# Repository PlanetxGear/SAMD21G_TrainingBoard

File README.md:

# Microchip SAMD21G Training Board for 「SAMファミリ活用ガイドブック」.
---
## Description
後閑哲也氏の著書[ＳＡＭファミリ活用ガイドブック][1](ISBN 978-4-297-11291-2)に出てくるトレーニングボードをKiCADで書き起こした回路図とガーバーデータです。
これは[KiCAD][2]によって描かれています。　この資料が皆さんの学習の一助となれば幸いです。

## Picture

## References.
 * <https://www.microchip.com/wwwproducts/en/ATsamd21g18>
 * <http://www.picfun.com/picbookZ3.html>
 * <https://gihyo.jp/book/2020/978-4-297-11291-2>

## Licence
[MIT]<https://en.wikipedia.org/wiki/MIT_License> <https://ja.wikipedia.org/wiki/MIT_License>

## Author
Hiroshi Murakami  
<https://www.planetxgear.com/>  

[1]: https://gihyo.jp/book/2020/978-4-297-11291-2 
[2]: https://kicad-pcb.org/

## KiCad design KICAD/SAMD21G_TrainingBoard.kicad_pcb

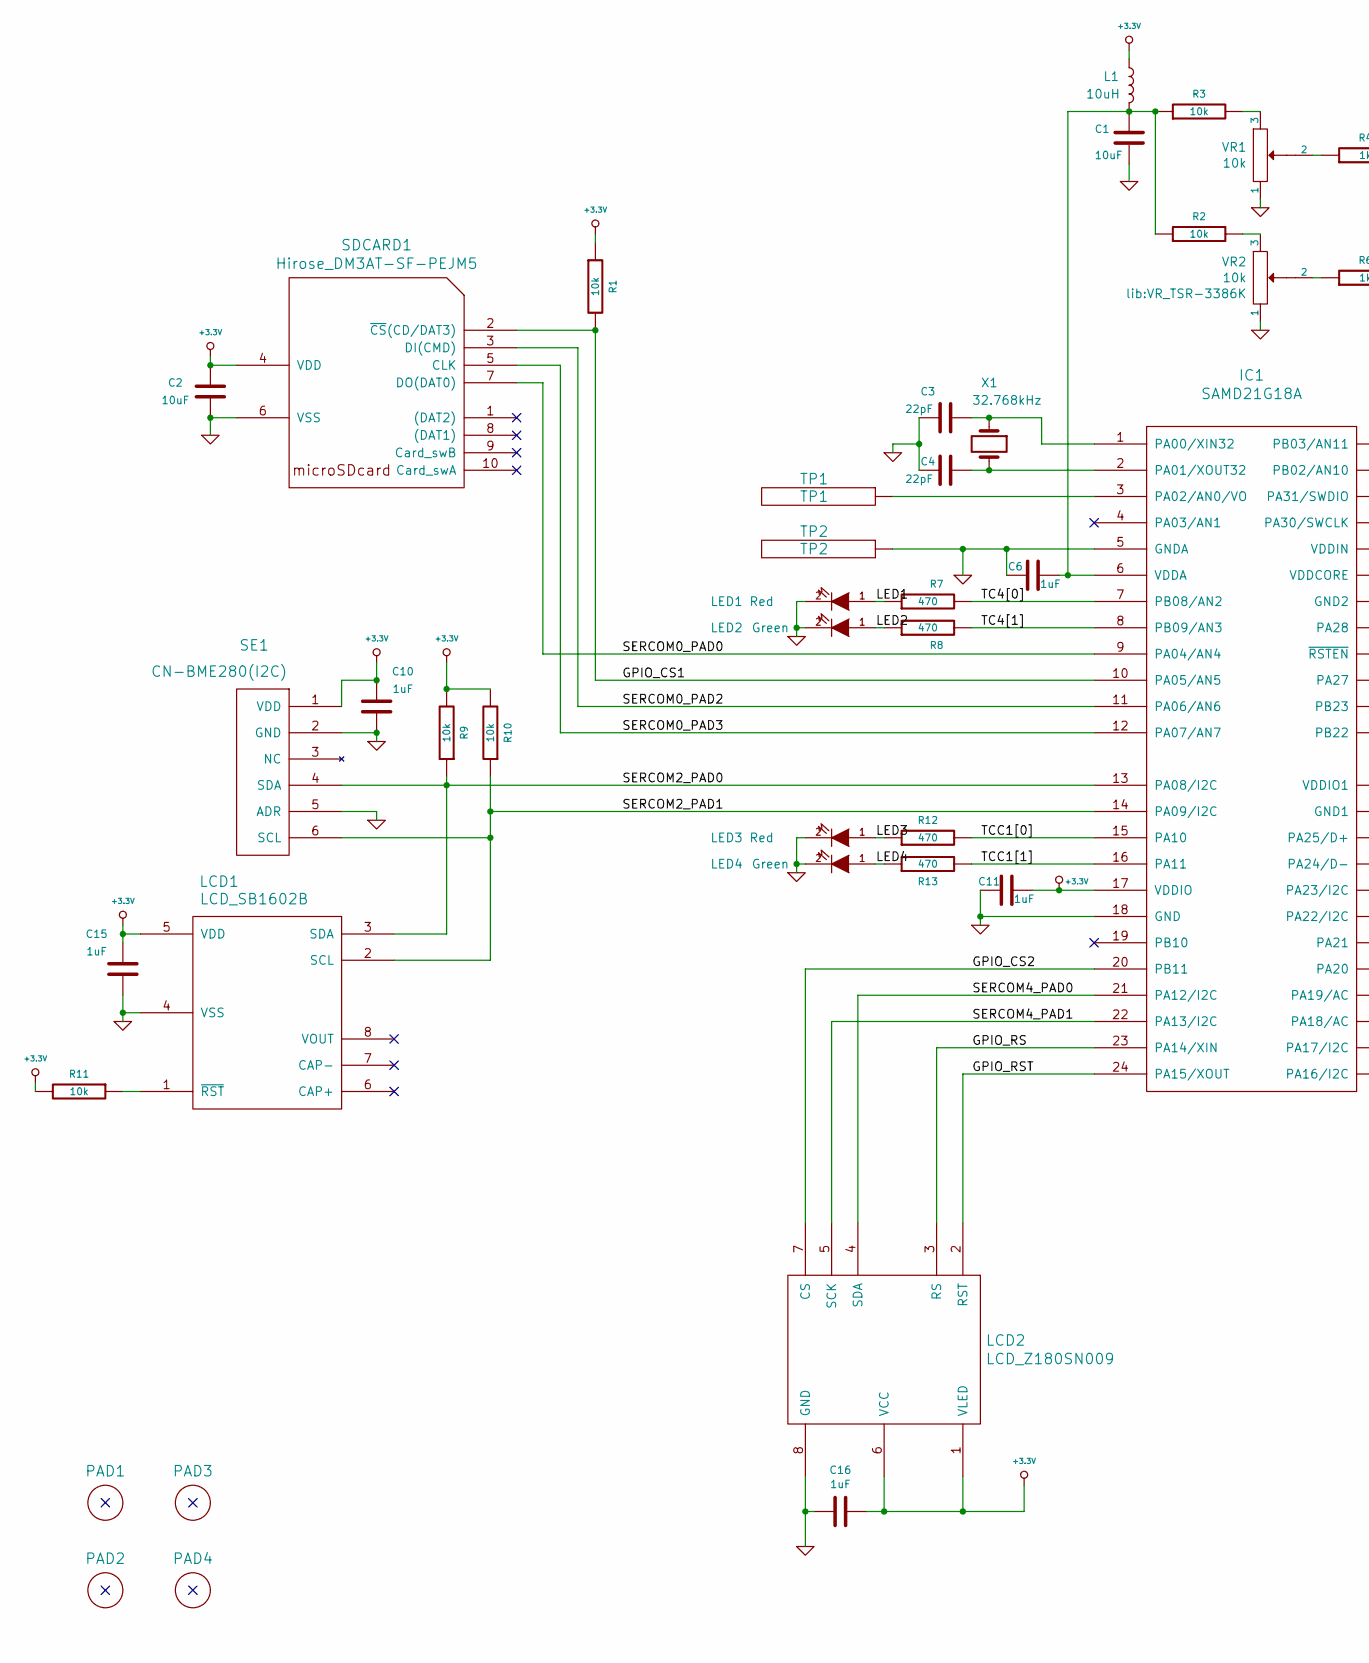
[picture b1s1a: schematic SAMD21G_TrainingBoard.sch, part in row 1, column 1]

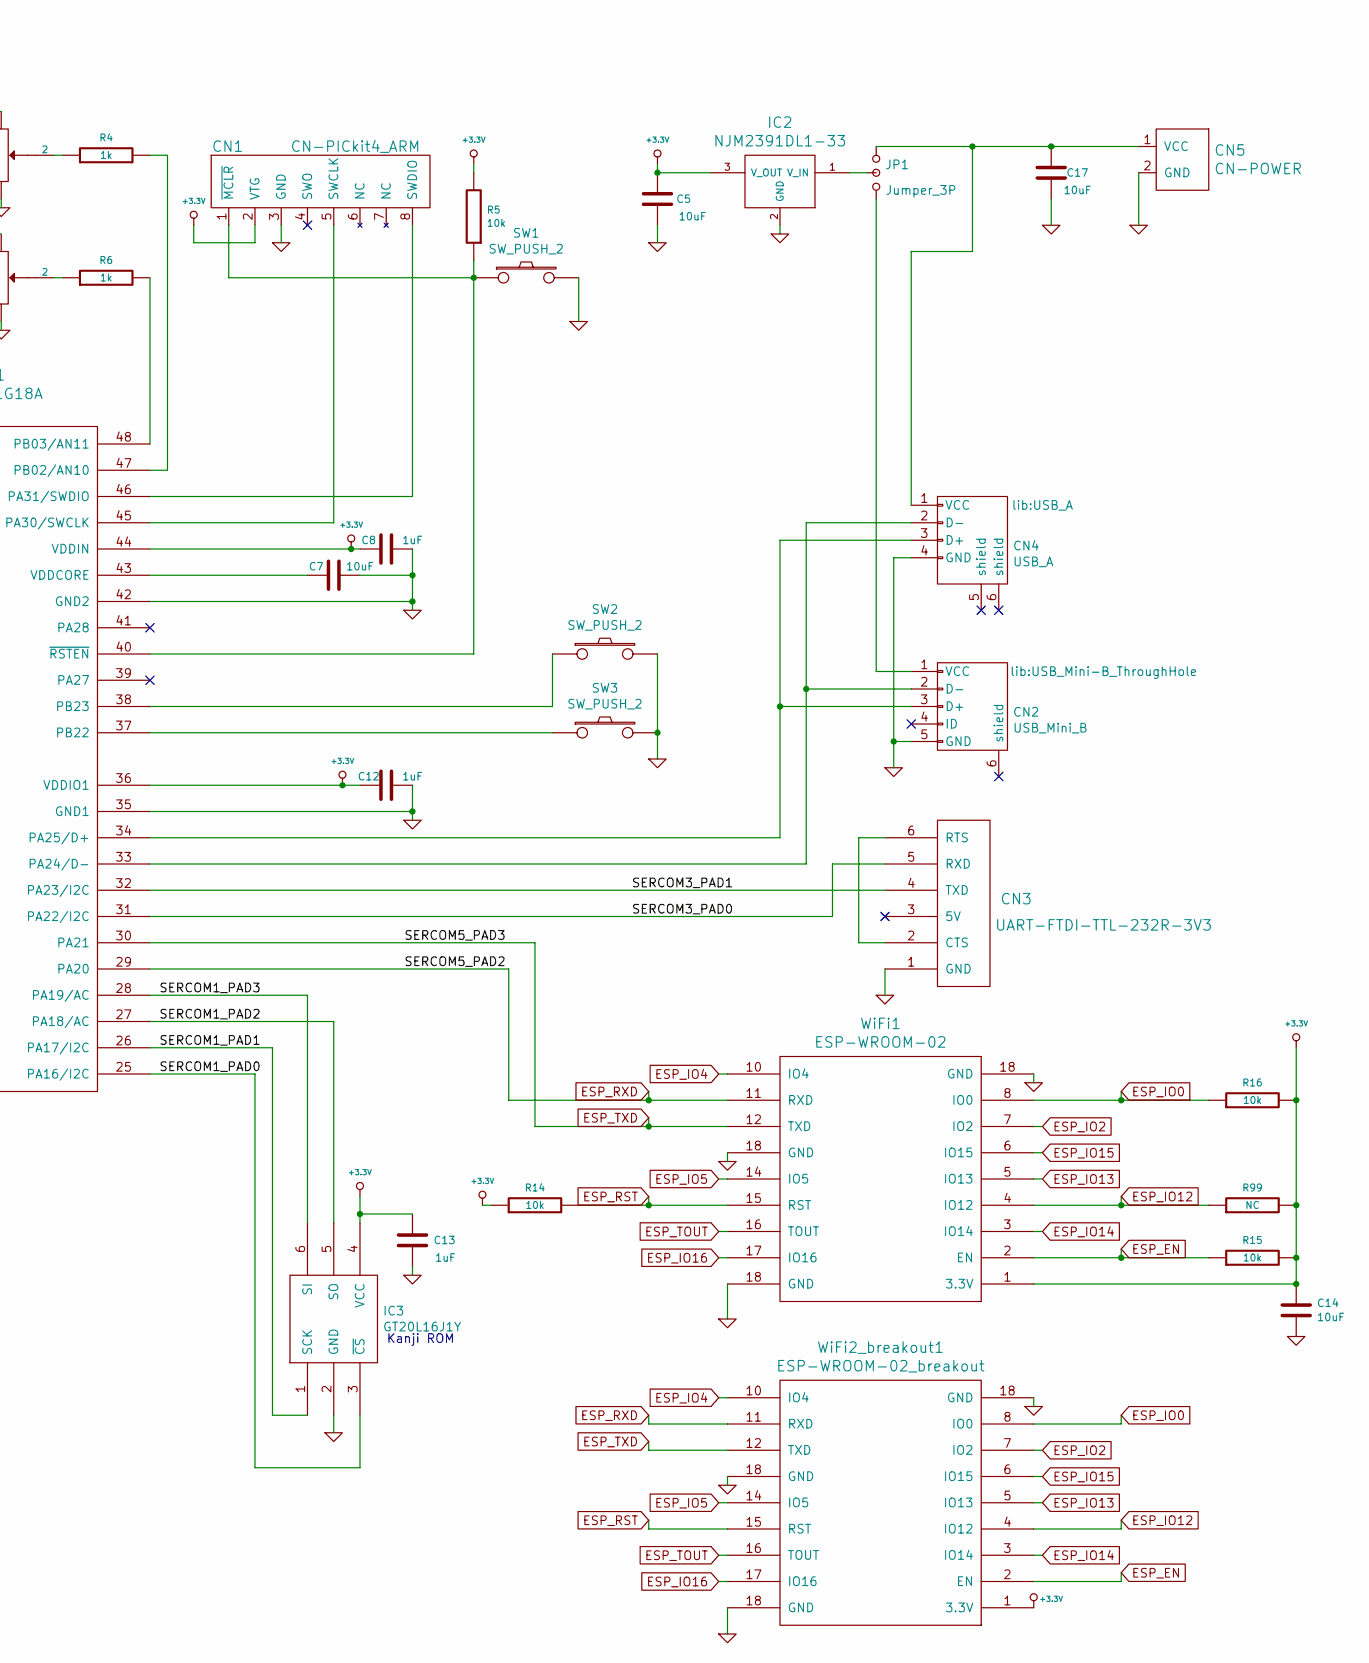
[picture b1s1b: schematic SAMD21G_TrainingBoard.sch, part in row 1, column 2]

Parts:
C1, C2, C5, C7, C14, C17: 10uF; C2_MU
C3, C4: 22pF; C2_MU
C6, C8, C10, C11, C12, C13, C15, C16: 1uF; C2_MU
CN1: CN-PICkit4_ARM; PINHEAD1-PICkit4_ARM
CN2: USB_Mini_B; USB_Mini-B_ThroughHole
CN3: UART-FTDI-TTL-232R-3V3; PINHEAD1-FTDI-TTL-232R-3V3
CN4: USB_A
CN5: CN-POWER; PINHEAD1-2_MU2
IC1: SAMD21G18A; TQFP-48_7x7mm_Pitch0.5mm
IC2: NJM2391DL1-33; TO-252-2
IC3: GT20L16J1Y; SOT-23-6_Handsoldering
JP1: Jumper_3P; JUMPER1-3
L1: 10uH; L4_MU
LCD1: LCD_SB1602B
LCD2: LCD_Z180SN009
LED1, LED3: Red; LED-5MM_AK
LED2, LED4: Green; LED-5MM_AK
PAD1, PAD2, PAD3, PAD4: PAD; PAD3mmX5mm
R1, R2, R3, R5, R9, R10, R11, R14, R15, R16: 10k; R4_MU
R4, R6: 1k; R4_MU
R7, R8, R12, R13: 470; R4_MU
R99: NC; R4_MU
SDCARD1: Hirose_DM3AT-SF-PEJM5; SD_CARD_microsdSD_HC_Hirose_DM3AT-SF-PEJM5
SE1: CN-BME280(I2C); CN_BME280(I2C)
SW1, SW2, SW3: SW_PUSH_2; SW_PUSH-6mm_AK
TP1: TP1; PAD1.6mmX3m
TP2: TP2; PAD1.6mmX3m
VR1, VR2: 10k; VR_TSR-3386K
WiFi1: ESP-WROOM-02
WiFi2_breakout1: ESP-WROOM-02_breakout
X1: 32.768kHz; X_TAL_VT200

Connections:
+3.3V: C2.2, C5.2, C8.2, C10.2, C11.1, C12.2, C13.1, C14.2, C15.2, C16.1, CN1.2 (VTG), IC1.17 (VDDIO), IC1.36 (VDDIO1), IC1.44 (VDDIN), IC2.3 (V_OUT), IC3.4 (VCC), L1.1, LCD1.5 (VDD), LCD2.1 (VLED), LCD2.6 (VCC), R1.1, R5.2, R9.2, R10.2, R11.2, R14.1, R15.2, R16.2, R99.2, SDCARD1.4 (VDD), SE1.1 (VDD), WiFi1.1 (3.3V), WiFi2_breakout1.1 (3.3V)
/GPIO_CS1: IC1.10 (PA05/AN5), R1.2, SDCARD1.2 (~CS~(CD/DAT3))
/GPIO_CS2: IC1.20 (PB11), LCD2.7 (CS)
/GPIO_RS: IC1.23 (PA14/XIN), LCD2.3 (RS)
/GPIO_RST: IC1.24 (PA15/XOUT), LCD2.2 (RST)
/LED1: LED1.1 (A), R7.1
/LED2: LED2.1 (A), R8.1
/LED3: LED3.1 (A), R12.1
/LED4: LED4.1 (A), R13.1
/SERCOM0_PAD0: IC1.9 (PA04/AN4), SDCARD1.7 (DO(DAT0))
/SERCOM0_PAD2: IC1.11 (PA06/AN6), SDCARD1.3 (DI(CMD))
/SERCOM0_PAD3: IC1.12 (PA07/AN7), SDCARD1.5 (CLK)
/SERCOM1_PAD0: IC1.25 (PA16/I2C), IC3.3 (~CS)
/SERCOM1_PAD1: IC1.26 (PA17/I2C), IC3.1 (SCK)
/SERCOM1_PAD2: IC1.27 (PA18/AC), IC3.5 (SO)
/SERCOM1_PAD3: IC1.28 (PA19/AC), IC3.6 (SI)
/SERCOM2_PAD0: IC1.13 (PA08/I2C), LCD1.3 (SDA), R9.1, SE1.4 (SDA)
/SERCOM2_PAD1: IC1.14 (PA09/I2C), LCD1.2 (SCL), R10.1, SE1.6 (SCL)
/SERCOM3_PAD0: CN3.5 (RXD), IC1.31 (PA22/I2C)
/SERCOM3_PAD1: CN3.4 (TXD), IC1.32 (PA23/I2C)
/SERCOM4_PAD0: IC1.21 (PA12/I2C), LCD2.4 (SDA)
/SERCOM4_PAD1: IC1.22 (PA13/I2C), LCD2.5 (SCK)
/TC4[0]: IC1.7 (PB08/AN2), R7.2
/TC4[1]: IC1.8 (PB09/AN3), R8.2
/TCC1[0]: IC1.15 (PA10), R12.2
/TCC1[1]: IC1.16 (PA11), R13.2
ESP_EN: R15.1, WiFi1.2 (EN), WiFi2_breakout1.2 (EN)
ESP_IO0: R16.1, WiFi1.8 (IO0), WiFi2_breakout1.8 (IO0)
ESP_IO2: WiFi1.7 (IO2), WiFi2_breakout1.7 (IO2)
ESP_IO4: WiFi1.10 (IO4), WiFi2_breakout1.10 (IO4)
ESP_IO5: WiFi1.14 (IO5), WiFi2_breakout1.14 (IO5)
ESP_IO12: R99.1, WiFi1.4 (IO12), WiFi2_breakout1.4 (IO12)
ESP_IO13: WiFi1.5 (IO13), WiFi2_breakout1.5 (IO13)
ESP_IO14: WiFi1.3 (IO14), WiFi2_breakout1.3 (IO14)
ESP_IO15: WiFi1.6 (IO15), WiFi2_breakout1.6 (IO15)
ESP_IO16: WiFi1.17 (IO16), WiFi2_breakout1.17 (IO16)
ESP_RST: R14.2, WiFi1.15 (RST), WiFi2_breakout1.15 (RST)
ESP_RXD: IC1.29 (PA20), WiFi1.11 (RXD), WiFi2_breakout1.11 (RXD)
ESP_TOUT: WiFi1.16 (TOUT), WiFi2_breakout1.16 (TOUT)
ESP_TXD: IC1.30 (PA21), WiFi1.12 (TXD), WiFi2_breakout1.12 (TXD)
GND: C1.2, C2.1, C3.2, C4.2, C5.1, C6.2, C7.1, C8.1, C10.1, C11.2, C12.1, C13.2, C14.1, C15.1, C16.2, C17.1, CN1.3 (GND), CN2.5 (GND), CN3.1 (GND), CN4.4 (GND), CN5.2 (GND), IC1.5 (GNDA), IC1.18 (GND), IC1.35 (GND1), IC1.42 (GND2), IC2.2 (GND), IC3.2 (GND), LCD1.4 (VSS), LCD2.8 (GND), LED1.2 (K), LED2.2 (K), LED3.2 (K), LED4.2 (K), SDCARD1.6 (VSS), SE1.2 (GND), SE1.5 (ADR), SW1.2, SW2.2, SW3.2, TP2.1, VR1.1, VR2.1, WiFi1.18 (GND), WiFi2_breakout1.18 (GND)
unnamed: C1.1, C6.1, IC1.6 (VDDA), L1.2, R2.1, R3.1
unnamed: C3.1, IC1.1 (PA00/XIN32), X1.1
unnamed: C4.1, IC1.2 (PA01/XOUT32), X1.2
unnamed: C7.2, IC1.43 (VDDCORE)
unnamed: C17.2, CN4.1 (VCC), CN5.1 (VCC), JP1.1
unnamed: CN1.1 (~MCLR), IC1.40 (~RSTEN), R5.1, SW1.1
unnamed: CN1.5 (SWCLK), IC1.45 (PA30/SWCLK)
unnamed: CN1.8 (SWDIO), IC1.46 (PA31/SWDIO)
unnamed: CN2.1 (VCC), JP1.3
unnamed: CN2.2 (D-), CN4.2 (D-), IC1.33 (PA24/D-)
unnamed: CN2.3 (D+), CN4.3 (D+), IC1.34 (PA25/D+)
unnamed: CN3.2 (CTS), CN3.6 (RTS)
unnamed: IC1.3 (PA02/AN0/VO), TP1.1
unnamed: IC1.37 (PB22), SW3.1
unnamed: IC1.38 (PB23), SW2.1
unnamed: IC1.47 (PB02/AN10), R4.2
unnamed: IC1.48 (PB03/AN11), R6.2
unnamed: IC2.1 (V_IN), JP1.2
unnamed: LCD1.1 (~RST), R11.1
unnamed: R2.2, VR2.3
unnamed: R3.2, VR1.3
unnamed: R4.1, VR1.2
unnamed: R6.1, VR2.2

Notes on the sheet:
Kanji ROM

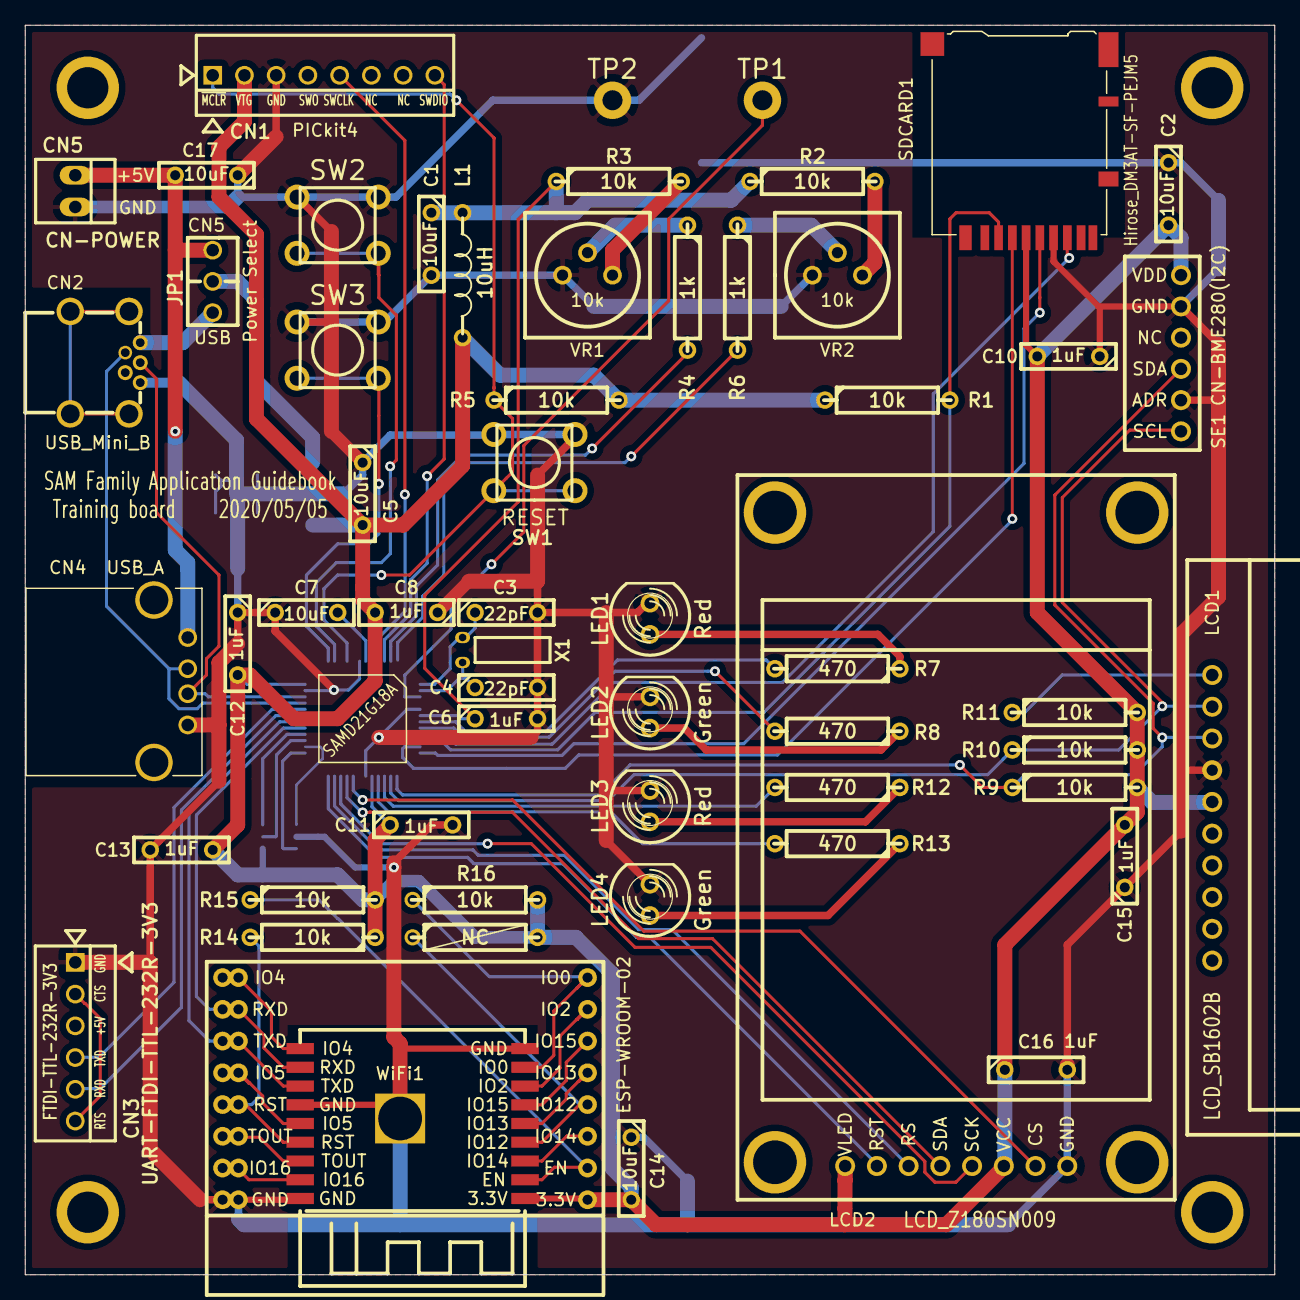
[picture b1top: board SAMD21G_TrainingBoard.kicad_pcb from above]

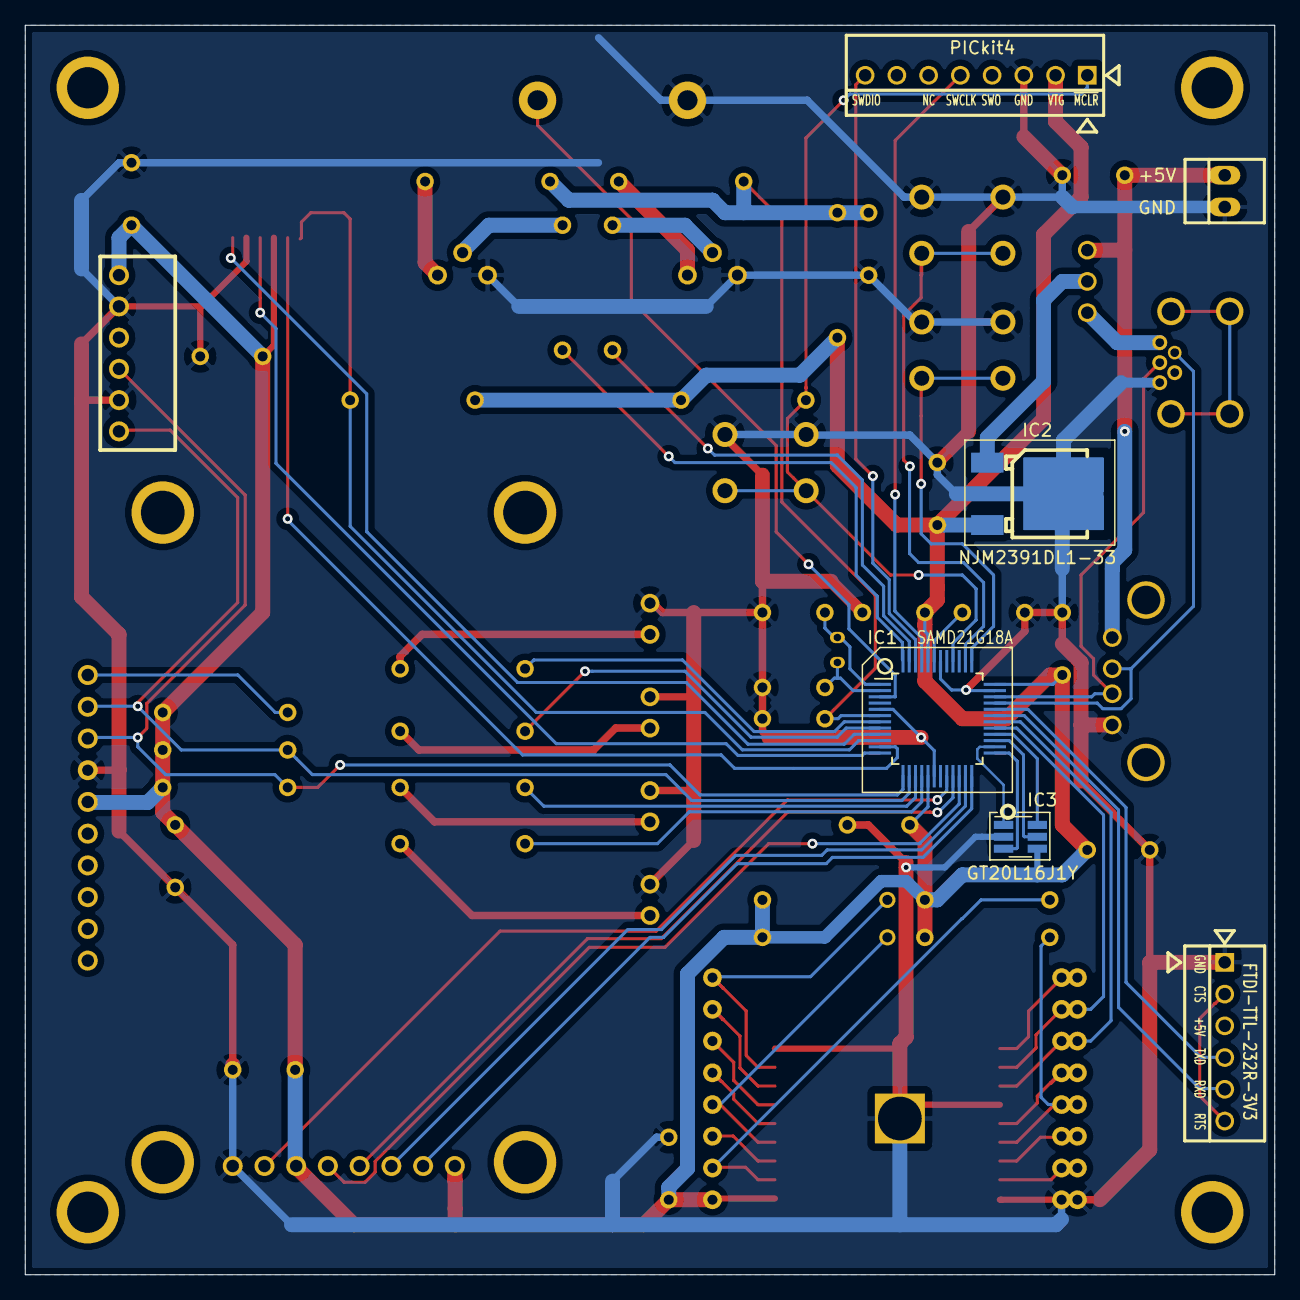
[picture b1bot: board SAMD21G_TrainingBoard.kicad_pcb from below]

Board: 2 copper layers, 100.0 x 100.0 mm, 65 parts (5 on the bottom side), 64 nets.

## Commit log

2020-05-10 amended some mistake in README.md
2020-05-10 amended README.md
2020-05-27 amend USB Type A connector Power Supply
